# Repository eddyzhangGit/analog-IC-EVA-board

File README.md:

Imagine that you are an integrated circuit designer at university lab. You took 5 month to design a integrated chip and just get back from fabrication. you are excited to test it. You want to see whether it will power up and how much power it will consume at certain states.

In order to test it and you most likely will need the following to configure your chip.

 - A positive/negative bias voltage to bias the transistor. 
 - A precision bias current for your current mirror.
 - Digital host to load the chip register.
 - Adjustable Voltage supply to power the chip.
 - E load to set current consumptions.

Instead of spending a large amount of time designing all the biasing circuit your self 
or worse, you use a lab equipments such as Aglient power supply,  Total phase digital host, E-load which cost thousands of dollars.

Our Analog IC Equation Platform offers an solution for rapid IC Evaluation.

The board is equipped with 

- 4 x 50 mA and 2 x200 mA power supply 0.5V to 3V with current Sensing ability
- 4 x Positive Bias Voltage 0 -3 V with error less than 0.5mV
- 2 x Negative Bias Voltage -2.5 - 0 V with error less than 1mV
- 4 x Bias current 0 - 1000uA with error less than 0.5%
- 2 Programmable resistor, 2.5K and 10K, 256 taps each
- Digital that allows GPIO and SPI communication.

The board is designed with a accuracy much higher than traditional lab Requirement,  to meet the requirement of IC testing

A MAC OS app is developed to allow user to  configure the board with ease.

Lastly, python functions are available to allow user to write their own scripts for automated testing. 
(Detailed Examples are provided in the USER MANUEL)
 
if you found this board will be beneficial to your project, Feel free to contact me for more information.

Eddy Zhen Zhang

Eddy.zhang@mail.utoronto.ca
 | 647-676-8287

￼

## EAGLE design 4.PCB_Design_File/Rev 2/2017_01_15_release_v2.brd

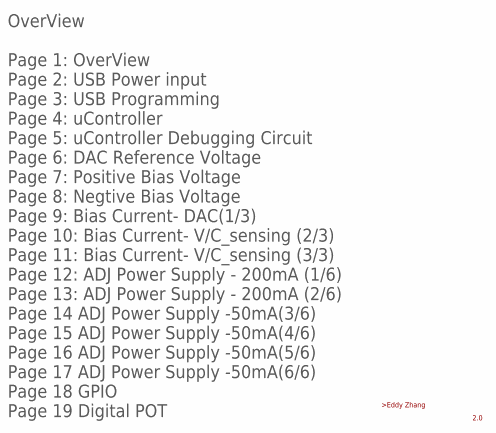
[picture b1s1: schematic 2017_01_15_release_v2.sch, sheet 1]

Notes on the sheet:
OverView Page 1: OverView Page 2: USB Power input Page 3: USB Programming Page 4: uController Page 5: uController Debugging Circuit Page 6: DAC Reference Voltage Page 7: Positive Bias Voltage Page 8: Negtive Bias Voltage Page 9: Bias Current- DAC(1/3) Page 10: Bias Current- V/C_sensing (2/3) Page 1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

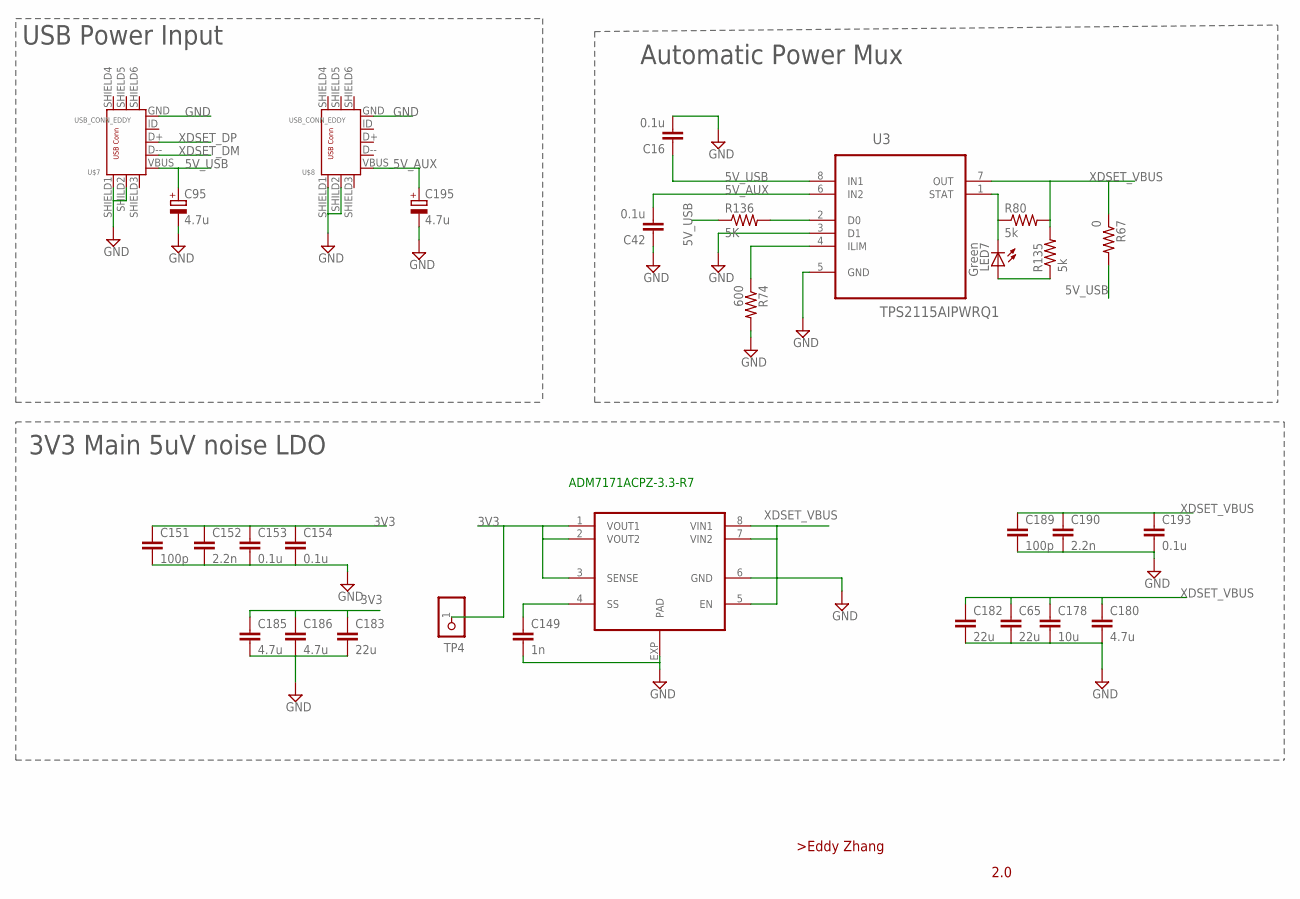
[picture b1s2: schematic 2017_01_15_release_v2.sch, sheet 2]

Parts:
C16, C42, C153, C154, C193: 0.1u; C0603
C65, C182, C183: 22u; C1210
C95, C195: 4.7u; A/3216-18R
C149: 1n; C0603
C151, C189: 100p; C0603
C152, C190: 2.2n; C0603
C178: 10u; C0805
C180, C185, C186: 4.7u; C0805
LED7: Green; LED-0603
R67: 0; R0603
R74: 600; R0603
R80, R135: 5k; R0603
R136: 5K; R0603
TP4: TEST_PIN2; 1X01
U3: TPS2115AIPWRQ1; SOP65P640X120-8N
U$7, U$8: USB_CONN_EDDY; USB_MICRO_EDDY
U$43: ADM7171; LFCSP8

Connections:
3V3: C151.1, C152.1, C153.1, C154.1, C183.1, C185.1, C186.1, TP4.1, U$43.1 (VOUT1), U$43.2 (VOUT2), U$43.3 (SENSE); also elsewhere on the board
5V_AUX: C42.2, C195.+, U3.6 (IN2), U$8.VBUS_ (VBUS); also elsewhere on the board
5V_USB: C16.1, C95.+, R67.2, R136.1, U3.8 (IN1), U$7.VBUS_ (VBUS); also elsewhere on the board
GND: C16.2, C42.1, C65.2, C95.-, C149.2, C151.2, C152.2, C153.2, C154.2, C178.2, C180.2, C182.2, C183.2, C185.2, C186.2, C189.2, C190.2, C193.2, C195.-, R74.2, U3.3 (D1), U3.5 (GND), U$7.GND, U$7.SHIELD1, U$7.SHILD2 (SHIELD2), U$8.GND, U$8.SHIELD1, U$8.SHILD2 (SHIELD2), U$43.6 (GND), U$43.EXP (PAD); also elsewhere on the board
unnamed: LED7.A, R135.1
unnamed: R136.2, U3.2 (D0)
unnamed: C149.1, U$43.4 (SS)
unnamed: LED7.C, R80.1, U3.1 (STAT)
unnamed: R74.1, U3.4 (ILIM)
XDSET_DM: U$7.D-- (D-); also elsewhere on the board
XDSET_DP: U$7.D+; also elsewhere on the board
XDSET_VBUS: C65.1, C178.1, C180.1, C182.1, C189.1, C190.1, C193.1, R67.1, R80.2, R135.2, U3.7 (OUT), U$43.5 (EN), U$43.7 (VIN2), U$43.8 (VIN1); also elsewhere on the board

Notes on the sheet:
USB Power Input
3V3 Main 5uV noise LDO
Automatic Power Mux
ADM7171ACPZ-3.3-R7

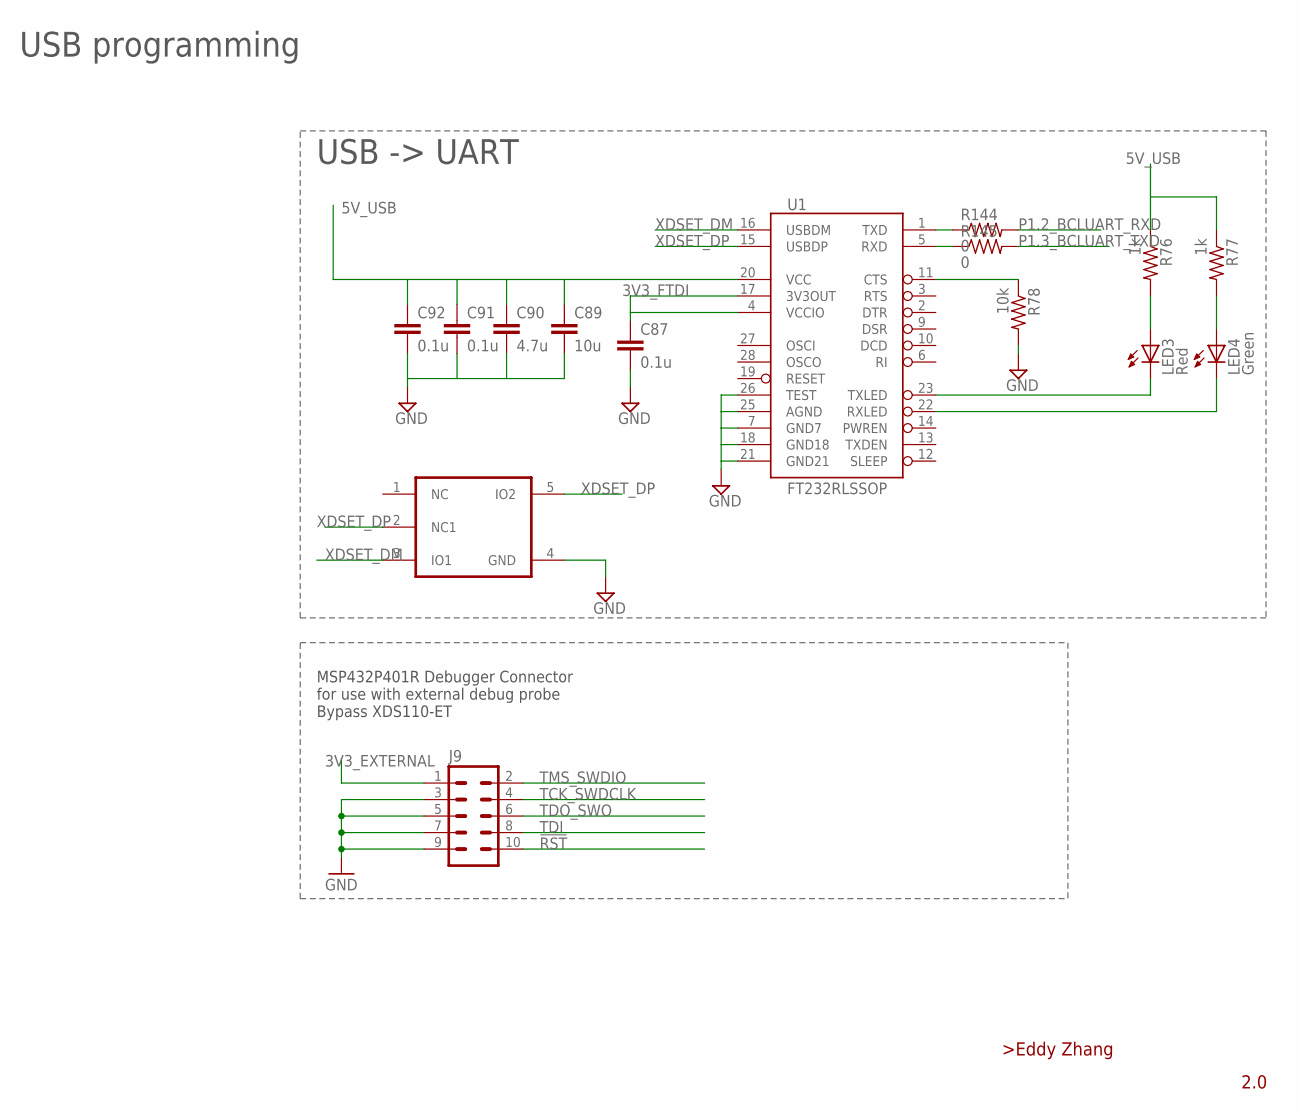
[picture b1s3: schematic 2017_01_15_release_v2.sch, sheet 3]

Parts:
C87, C91, C92: 0.1u; C0603
C89: 10u; C0805
C90: 4.7u; C0805
ESD_DIODE: TPD2E2U06; SOT_DRL_N5
J9: DEBUG_ARM-10; ARM-10
LED3: Red; LED-0603
LED4: Green; LED-0603
R76, R77: 1k; R0603
R78: 10k; R0603
R144, R145: 0; R0603
U1: FT232RLSSOP; SSOP28DB

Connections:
3V3_EXTERNAL: J9.1
3V3_FTDI: C87.1, U1.4 (VCCIO), U1.17 (3V3OUT)
5V_USB: C89.1, C90.1, C91.1, C92.1, R76.1, R77.1, U1.20 (VCC); also elsewhere on the board
!RST: J9.10; also elsewhere on the board
GND: C87.2, C89.2, C90.2, C91.2, C92.2, ESD_DIODE.4 (GND), J9.3, J9.5, J9.7, J9.9, R78.2, U1.7 (GND7), U1.18 (GND18), U1.21 (GND21), U1.25 (AGND), U1.26 (TEST); also elsewhere on the board
unnamed: R78.1, U1.11 (CTS)
unnamed: LED3.C, U1.23 (TXLED)
unnamed: LED4.C, U1.22 (RXLED)
unnamed: LED3.A, R76.2
unnamed: LED4.A, R77.2
P1.2_BCLUART_RXD: R144.2; also elsewhere on the board
P1.2_BCLUART_RXD_IC: R144.1, U1.1 (TXD)
P1.3_BCLUART_TXD: R145.2; also elsewhere on the board
P1.3_BCLUART_TXD_IC: R145.1, U1.5 (RXD)
TCK_SWDCLK: J9.4; also elsewhere on the board
TDI: J9.8; also elsewhere on the board
TDO_SWO: J9.6; also elsewhere on the board
TMS_SWDIO: J9.2; also elsewhere on the board
XDSET_DM: ESD_DIODE.3 (IO1), U1.16 (USBDM); also elsewhere on the board
XDSET_DP: ESD_DIODE.2 (NC1), ESD_DIODE.5 (IO2), U1.15 (USBDP); also elsewhere on the board

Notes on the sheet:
USB programming
USB -> UART
MSP432P401R Debugger Connector for use with external debug probe Bypass XDS110-ET

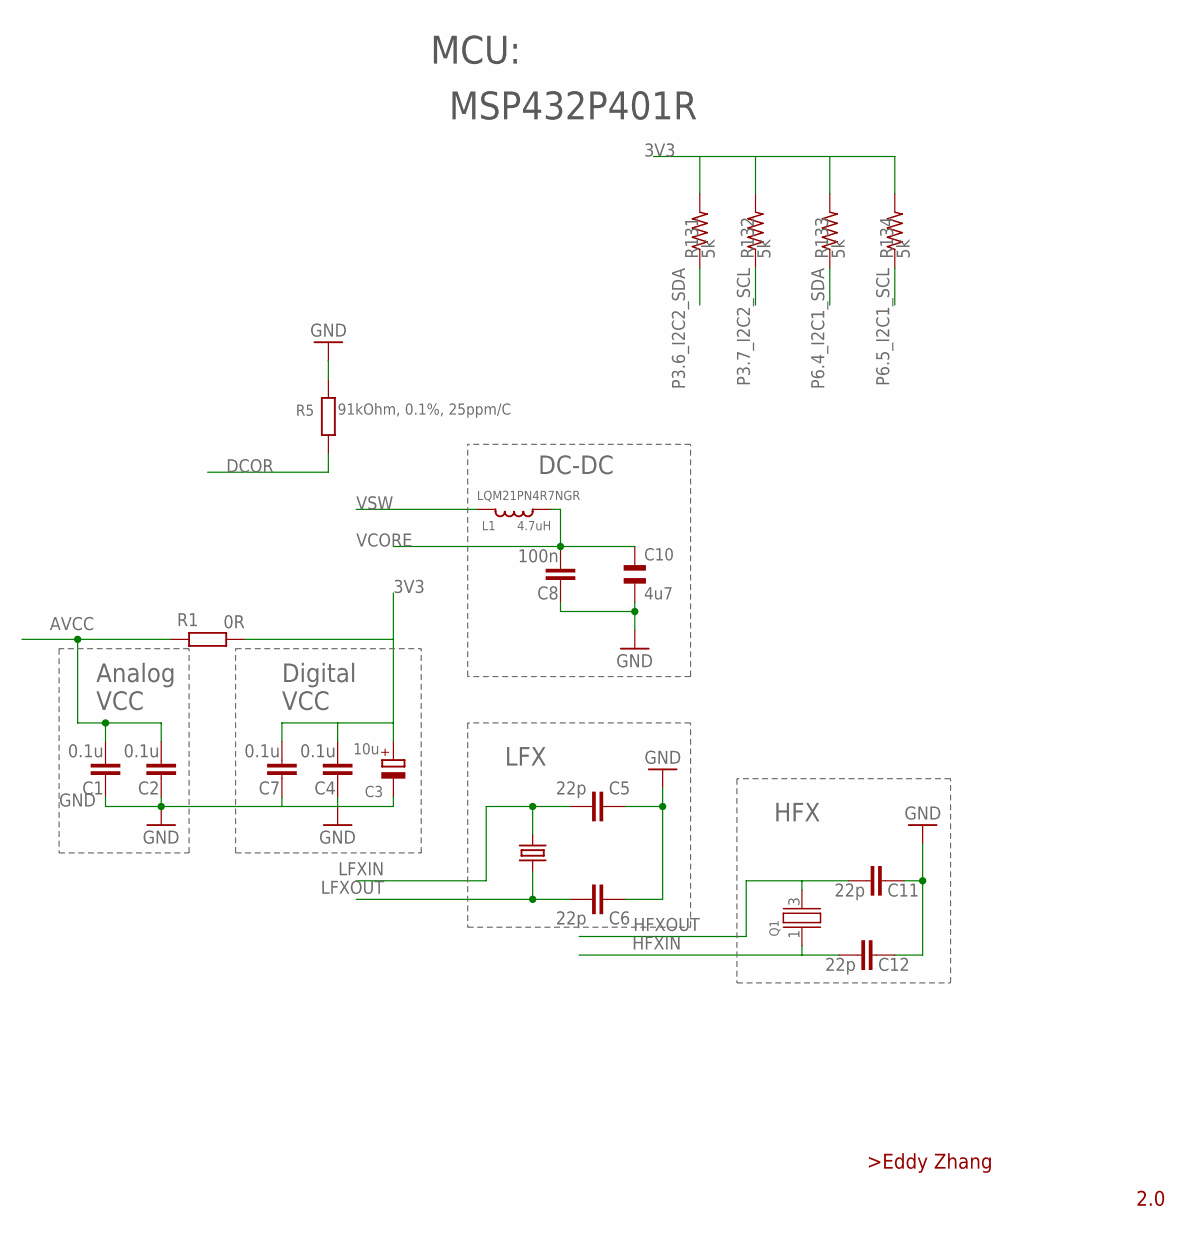
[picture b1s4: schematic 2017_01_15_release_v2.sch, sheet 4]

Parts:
32KHZ: FC-135; FC-135_32KHZ
C1, C2, C4, C7: 0.1u; C0603K
C3: 10u; A/3216-18R
C5, C6: 22p; C0603
C8: 100n; C0603K
C10: 4u7; CSMD0805
C11, C12: 22p; C0603K
L1: 4.7uH; 0806
Q1: CRYSTALEPSON_FA-238; FA-238
R1: 0R; R0603
R5: 91kOhm, 0.1%, 25ppm/C; 0805
R131, R132, R133, R134: 5k; R0603

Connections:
3V3: C3.+, C4.1, C7.1, R1.1, R131.2, R132.2, R133.2, R134.2; also elsewhere on the board
AVCC: C1.1, C2.1, R1.2; also elsewhere on the board
DCOR: R5.1; also elsewhere on the board
GND: C1.2, C2.2, C3.-, C4.2, C5.2, C6.2, C7.2, C8.2, C10.2, C11.2, C12.2, R5.2; also elsewhere on the board
HFXIN: C12.1, Q1.1; also elsewhere on the board
HFXOUT: C11.1, Q1.3 (2); also elsewhere on the board
LFXIN: 32KHZ.P$2 (2), C5.1; also elsewhere on the board
LFXOUT: 32KHZ.P$1 (1), C6.1; also elsewhere on the board
P3.6_I2C2_SDA: R131.1; also elsewhere on the board
P3.7_I2C2_SCL: R132.1; also elsewhere on the board
P6.4_I2C1_SDA: R133.1; also elsewhere on the board
P6.5_I2C1_SCL: R134.1; also elsewhere on the board
VCORE: C8.1, C10.1, L1.1; also elsewhere on the board
VSW: L1.2; also elsewhere on the board

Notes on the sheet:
MCU:
LQM21PN4R7NGR
HFX
LFX
Analog
VCC
Digital
DC-DC
MSP432P401R

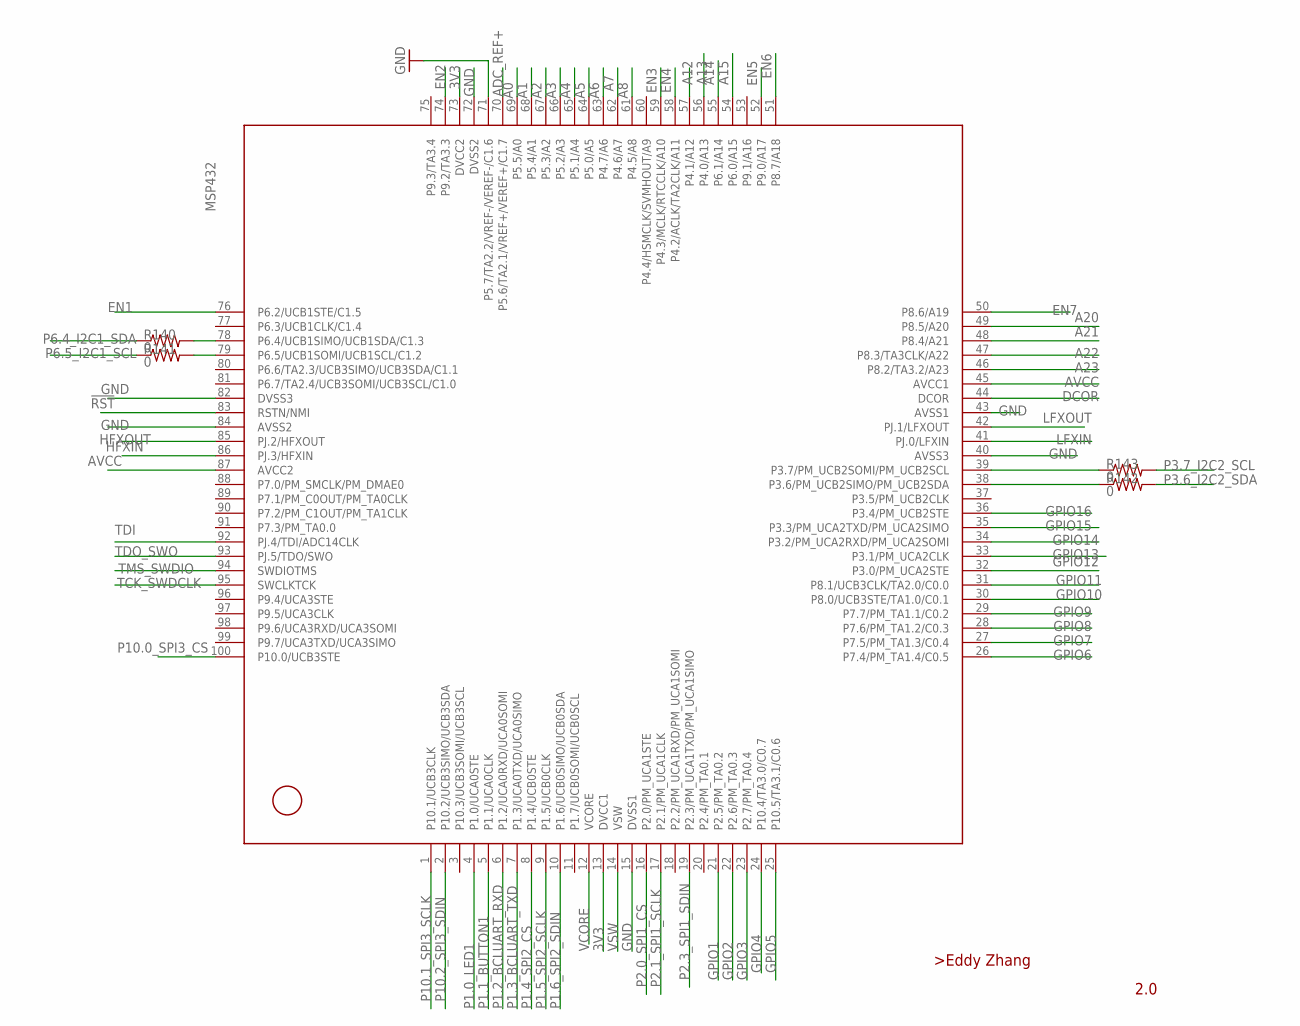
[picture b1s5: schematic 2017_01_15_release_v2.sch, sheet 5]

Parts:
MSP432: MSP432P401XPZ; LQFP100
R140, R141, R142, R143: 0; R0603

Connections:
3V3: MSP432.13 (DVCC1), MSP432.73 (DVCC2); also elsewhere on the board
!RST: MSP432.83 (RSTN/NMI); also elsewhere on the board
A0: MSP432.69 (P5.5/A0); also elsewhere on the board
A1: MSP432.68 (P5.4/A1); also elsewhere on the board
A2: MSP432.67 (P5.3/A2); also elsewhere on the board
A3: MSP432.66 (P5.2/A3); also elsewhere on the board
A4: MSP432.65 (P5.1/A4); also elsewhere on the board
A5: MSP432.64 (P5.0/A5); also elsewhere on the board
A6: MSP432.63 (P4.7/A6); also elsewhere on the board
A7: MSP432.62 (P4.6/A7); also elsewhere on the board
A8: MSP432.61 (P4.5/A8); also elsewhere on the board
A12: MSP432.57 (P4.1/A12); also elsewhere on the board
A13: MSP432.56 (P4.0/A13); also elsewhere on the board
A14: MSP432.55 (P6.1/A14); also elsewhere on the board
A15: MSP432.54 (P6.0/A15); also elsewhere on the board
A20: MSP432.49 (P8.5/A20); also elsewhere on the board
A21: MSP432.48 (P8.4/A21); also elsewhere on the board
A22: MSP432.47 (P8.3/TA3CLK/A22); also elsewhere on the board
A23: MSP432.46 (P8.2/TA3.2/A23); also elsewhere on the board
ADC_REF+: MSP432.70 (P5.6/TA2.1/VREF+/VEREF+/C1.7); also elsewhere on the board
AVCC: MSP432.45 (AVCC1), MSP432.87 (AVCC2); also elsewhere on the board
DCOR: MSP432.44 (DCOR); also elsewhere on the board
EN1: MSP432.76 (P6.2/UCB1STE/C1.5); also elsewhere on the board
EN2: MSP432.74 (P9.2/TA3.3); also elsewhere on the board
EN3: MSP432.59 (P4.3/MCLK/RTCCLK/A10); also elsewhere on the board
EN4: MSP432.58 (P4.2/ACLK/TA2CLK/A11); also elsewhere on the board
EN5: MSP432.52 (P9.0/A17); also elsewhere on the board
EN6: MSP432.51 (P8.7/A18); also elsewhere on the board
EN7: MSP432.50 (P8.6/A19); also elsewhere on the board
GND: MSP432.15 (DVSS1), MSP432.40 (AVSS3), MSP432.43 (AVSS1), MSP432.71 (P5.7/TA2.2/VREF-/VEREF-/C1.6), MSP432.72 (DVSS2), MSP432.82 (DVSS3), MSP432.84 (AVSS2); also elsewhere on the board
GPIO1: MSP432.21 (P2.5/PM_TA0.2); also elsewhere on the board
GPIO2: MSP432.22 (P2.6/PM_TA0.3); also elsewhere on the board
GPIO3: MSP432.23 (P2.7/PM_TA0.4); also elsewhere on the board
GPIO4: MSP432.24 (P10.4/TA3.0/C0.7); also elsewhere on the board
GPIO5: MSP432.25 (P10.5/TA3.1/C0.6); also elsewhere on the board
GPIO6: MSP432.26 (P7.4/PM_TA1.4/C0.5); also elsewhere on the board
GPIO7: MSP432.27 (P7.5/PM_TA1.3/C0.4); also elsewhere on the board
GPIO8: MSP432.28 (P7.6/PM_TA1.2/C0.3); also elsewhere on the board
GPIO9: MSP432.29 (P7.7/PM_TA1.1/C0.2); also elsewhere on the board
GPIO10: MSP432.30 (P8.0/UCB3STE/TA1.0/C0.1); also elsewhere on the board
GPIO11: MSP432.31 (P8.1/UCB3CLK/TA2.0/C0.0); also elsewhere on the board
GPIO12: MSP432.32 (P3.0/PM_UCA2STE); also elsewhere on the board
GPIO13: MSP432.33 (P3.1/PM_UCA2CLK); also elsewhere on the board
GPIO14: MSP432.34 (P3.2/PM_UCA2RXD/PM_UCA2SOMI); also elsewhere on the board
GPIO15: MSP432.35 (P3.3/PM_UCA2TXD/PM_UCA2SIMO); also elsewhere on the board
GPIO16: MSP432.36 (P3.4/PM_UCB2STE); also elsewhere on the board
HFXIN: MSP432.86 (PJ.3/HFXIN); also elsewhere on the board
HFXOUT: MSP432.85 (PJ.2/HFXOUT); also elsewhere on the board
LFXIN: MSP432.41 (PJ.0/LFXIN); also elsewhere on the board
LFXOUT: MSP432.42 (PJ.1/LFXOUT); also elsewhere on the board
P1.0_LED1: MSP432.4 (P1.0/UCA0STE); also elsewhere on the board
P1.1_BUTTON1: MSP432.5 (P1.1/UCA0CLK); also elsewhere on the board
P1.2_BCLUART_RXD: MSP432.6 (P1.2/UCA0RXD/UCA0SOMI); also elsewhere on the board
P1.3_BCLUART_TXD: MSP432.7 (P1.3/UCA0TXD/UCA0SIMO); also elsewhere on the board
P1.4_SPI2_CS: MSP432.8 (P1.4/UCB0STE); also elsewhere on the board
P1.5_SPI2_SCLK: MSP432.9 (P1.5/UCB0CLK); also elsewhere on the board
P1.6_SPI2_SDIN: MSP432.10 (P1.6/UCB0SIMO/UCB0SDA); also elsewhere on the board
P2.0_SPI1_CS: MSP432.16 (P2.0/PM_UCA1STE); also elsewhere on the board
P2.1_SPI1_SCLK: MSP432.17 (P2.1/PM_UCA1CLK); also elsewhere on the board
P2.3_SPI1_SDIN: MSP432.19 (P2.3/PM_UCA1TXD/PM_UCA1SIMO); also elsewhere on the board
P3.6_I2C2_SDA: R142.2; also elsewhere on the board
P3.6_I2C2_SDA_IC: MSP432.38 (P3.6/PM_UCB2SIMO/PM_UCB2SDA), R142.1
P3.7_I2C2_SCL: R143.2; also elsewhere on the board
P3.7_I2C2_SCL_IC: MSP432.39 (P3.7/PM_UCB2SOMI/PM_UCB2SCL), R143.1
P6.4_I2C1_SDA: R140.1; also elsewhere on the board
P6.4_I2C1_SDA_IC: MSP432.78 (P6.4/UCB1SIMO/UCB1SDA/C1.3), R140.2
P6.5_I2C1_SCL: R141.1; also elsewhere on the board
P6.5_I2C1_SCL_IC: MSP432.79 (P6.5/UCB1SOMI/UCB1SCL/C1.2), R141.2
P10.0_SPI3_CS: MSP432.100 (P10.0/UCB3STE); also elsewhere on the board
P10.1_SPI3_SCLK: MSP432.1 (P10.1/UCB3CLK); also elsewhere on the board
P10.2_SPI3_SDIN: MSP432.2 (P10.2/UCB3SIMO/UCB3SDA); also elsewhere on the board
TCK_SWDCLK: MSP432.95 (SWCLKTCK); also elsewhere on the board
TDI: MSP432.92 (PJ.4/TDI/ADC14CLK); also elsewhere on the board
TDO_SWO: MSP432.93 (PJ.5/TDO/SWO); also elsewhere on the board
TMS_SWDIO: MSP432.94 (SWDIOTMS); also elsewhere on the board
VCORE: MSP432.12 (VCORE); also elsewhere on the board
VSW: MSP432.14 (VSW); also elsewhere on the board

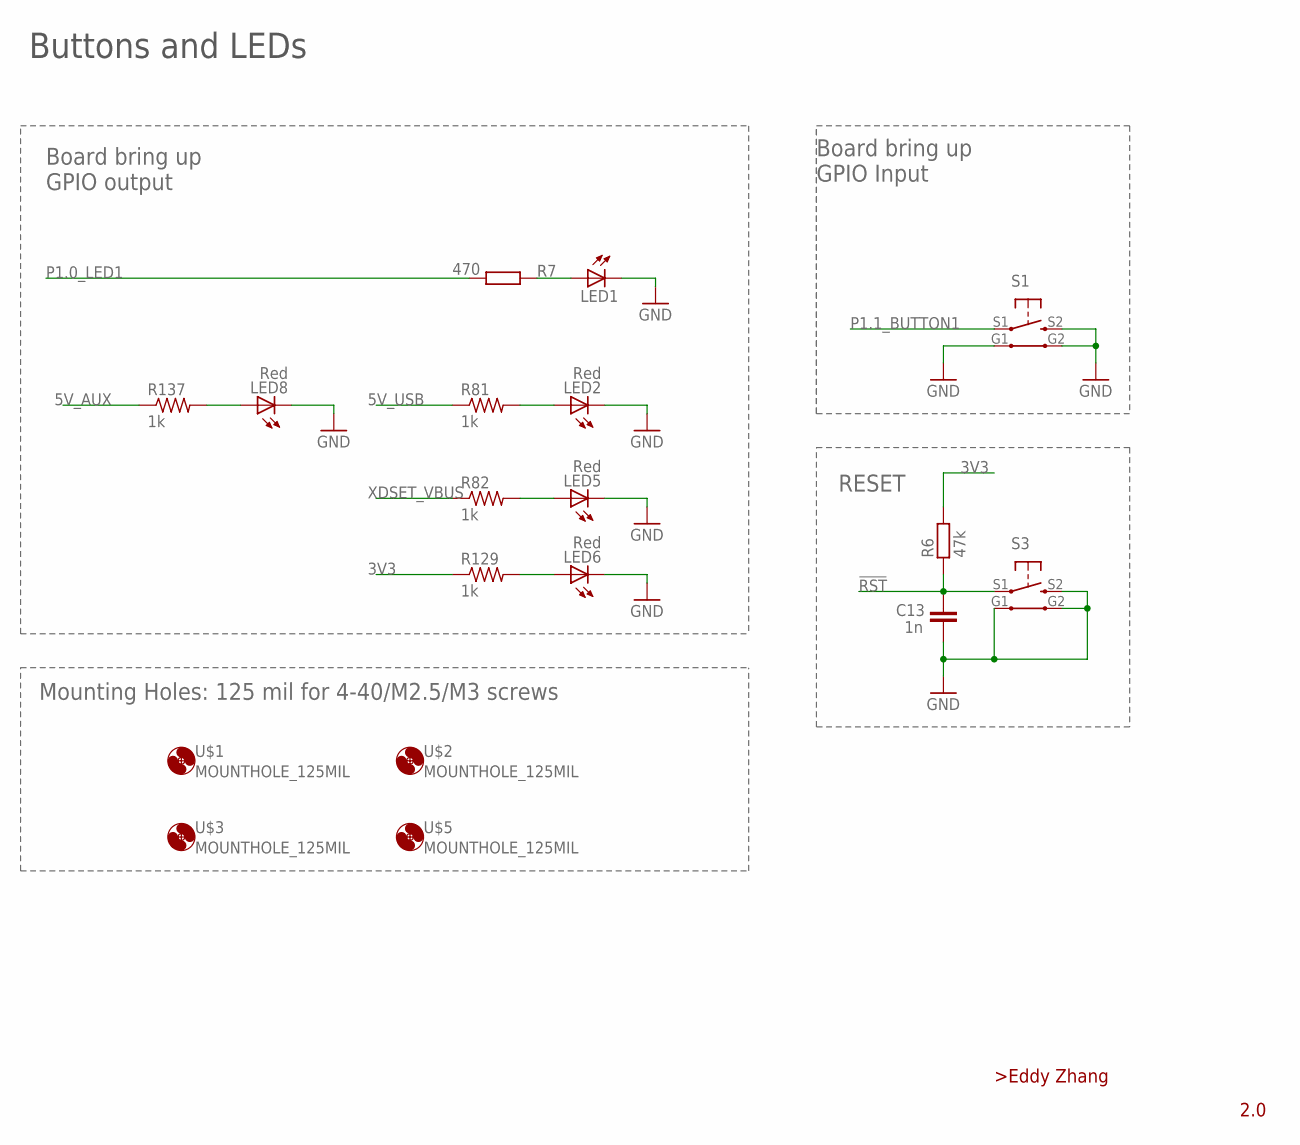
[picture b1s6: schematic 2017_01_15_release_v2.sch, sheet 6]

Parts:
C13: 1n; C0603
LED1: LEDCHIPLED_0603; CHIPLED_0603
LED2, LED5, LED6, LED8: Red; LED-0603
R6: 47k; R0603
R7: 470; R0603
R81, R82, R129, R137: 1k; R0603
S1, S3: TS-1188E
U$1, U$2, U$3, U$5: MOUNTHOLE_125MIL

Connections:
3V3: R6.2, R129.1; also elsewhere on the board
5V_AUX: R137.1; also elsewhere on the board
5V_USB: R81.1; also elsewhere on the board
!RST: C13.1, R6.1, S3.S1; also elsewhere on the board
GND: C13.2, LED1.C, LED2.C, LED5.C, LED6.C, LED8.C, S1.G1, S1.G2, S1.S2 (S), S3.G1, S3.G2, S3.S2 (S); also elsewhere on the board
unnamed: LED1.A, R7.2
unnamed: LED8.A, R137.2
unnamed: LED6.A, R129.2
unnamed: LED2.A, R81.2
unnamed: LED5.A, R82.2
P1.0_LED1: R7.1; also elsewhere on the board
P1.1_BUTTON1: S1.S1; also elsewhere on the board
XDSET_VBUS: R82.1; also elsewhere on the board

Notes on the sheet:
Board bring up GPIO Input
RESET
Buttons and LEDs
Mounting Holes: 125 mil for 4-40/M2.5/M3 screws
Board bring up GPIO output

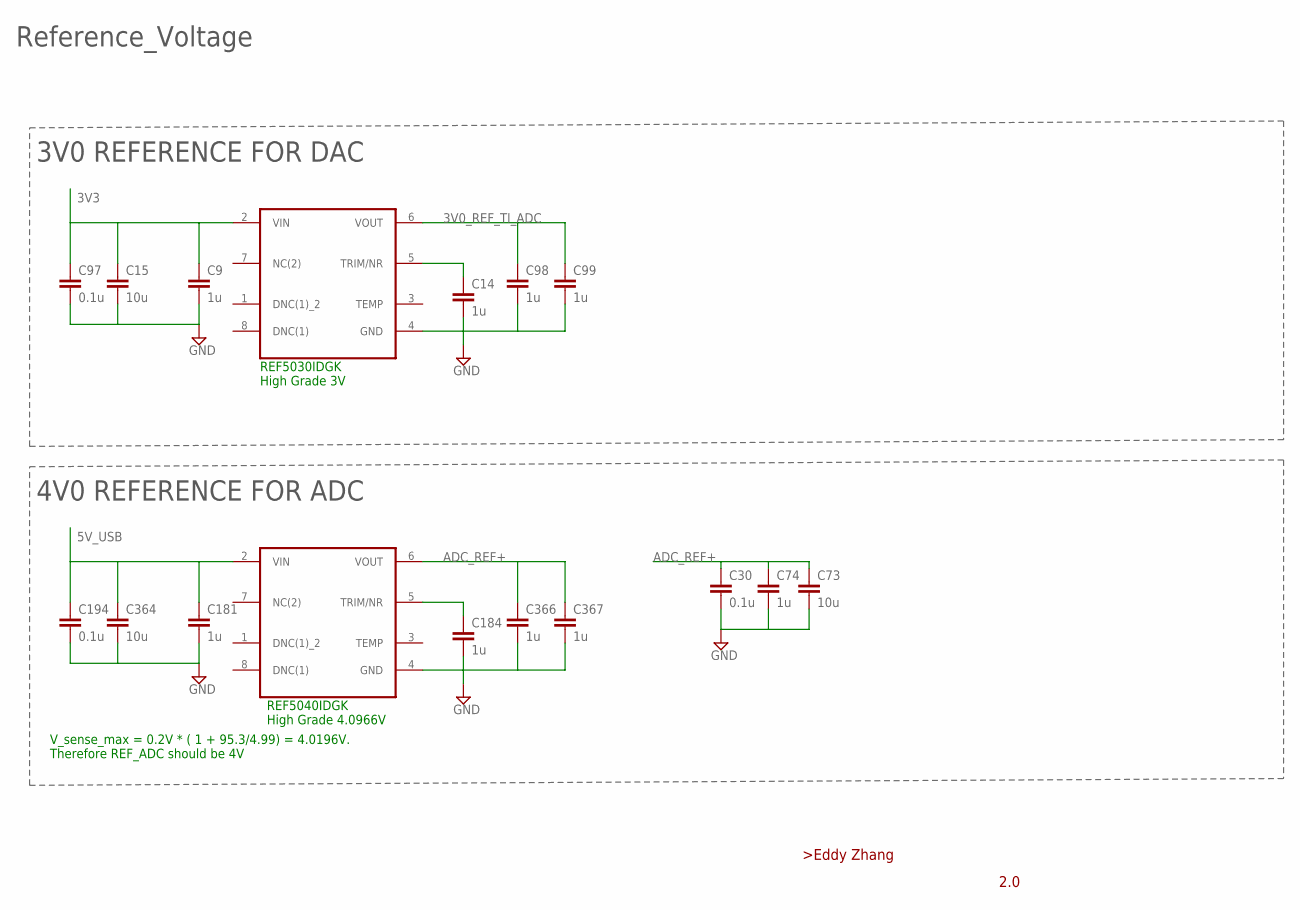
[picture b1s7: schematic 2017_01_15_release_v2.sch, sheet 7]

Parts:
C9, C98, C99, C181, C184, C366, C367: 1u; C0603
C14, C74: 1u; C0603K
C15, C364: 10u; C0805
C30: 0.1u; C0603K
C73: 10u; C0805K
C97, C194: 0.1u; C0603
REF5030, REF5040: REF5025AID; SOIC127P600X175-8N

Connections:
3V0_REF_TI_ADC: C98.1, C99.1, REF5030.6 (VOUT); also elsewhere on the board
3V3: C9.1, C15.1, C97.1, REF5030.2 (VIN); also elsewhere on the board
5V_USB: C181.1, C194.1, C364.1, REF5040.2 (VIN); also elsewhere on the board
ADC_REF+: C30.1, C73.1, C74.1, C366.1, C367.1, REF5040.6 (VOUT); also elsewhere on the board
GND: C9.2, C14.2, C15.2, C30.2, C73.2, C74.2, C97.2, C98.2, C99.2, C181.2, C184.2, C194.2, C364.2, C366.2, C367.2, REF5030.4 (GND), REF5040.4 (GND); also elsewhere on the board
unnamed: C14.1, REF5030.5 (TRIM/NR)
unnamed: C184.1, REF5040.5 (TRIM/NR)

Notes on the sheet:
Reference_Voltage
3V0 REFERENCE FOR DAC
4V0 REFERENCE FOR ADC
V_sense_max = 0.2V * ( 1 + 95.3/4.99) = 4.0196V. Therefore REF_ADC should be 4V
REF5040IDGK High Grade 4.0966V
REF5030IDGK High Grade 3V

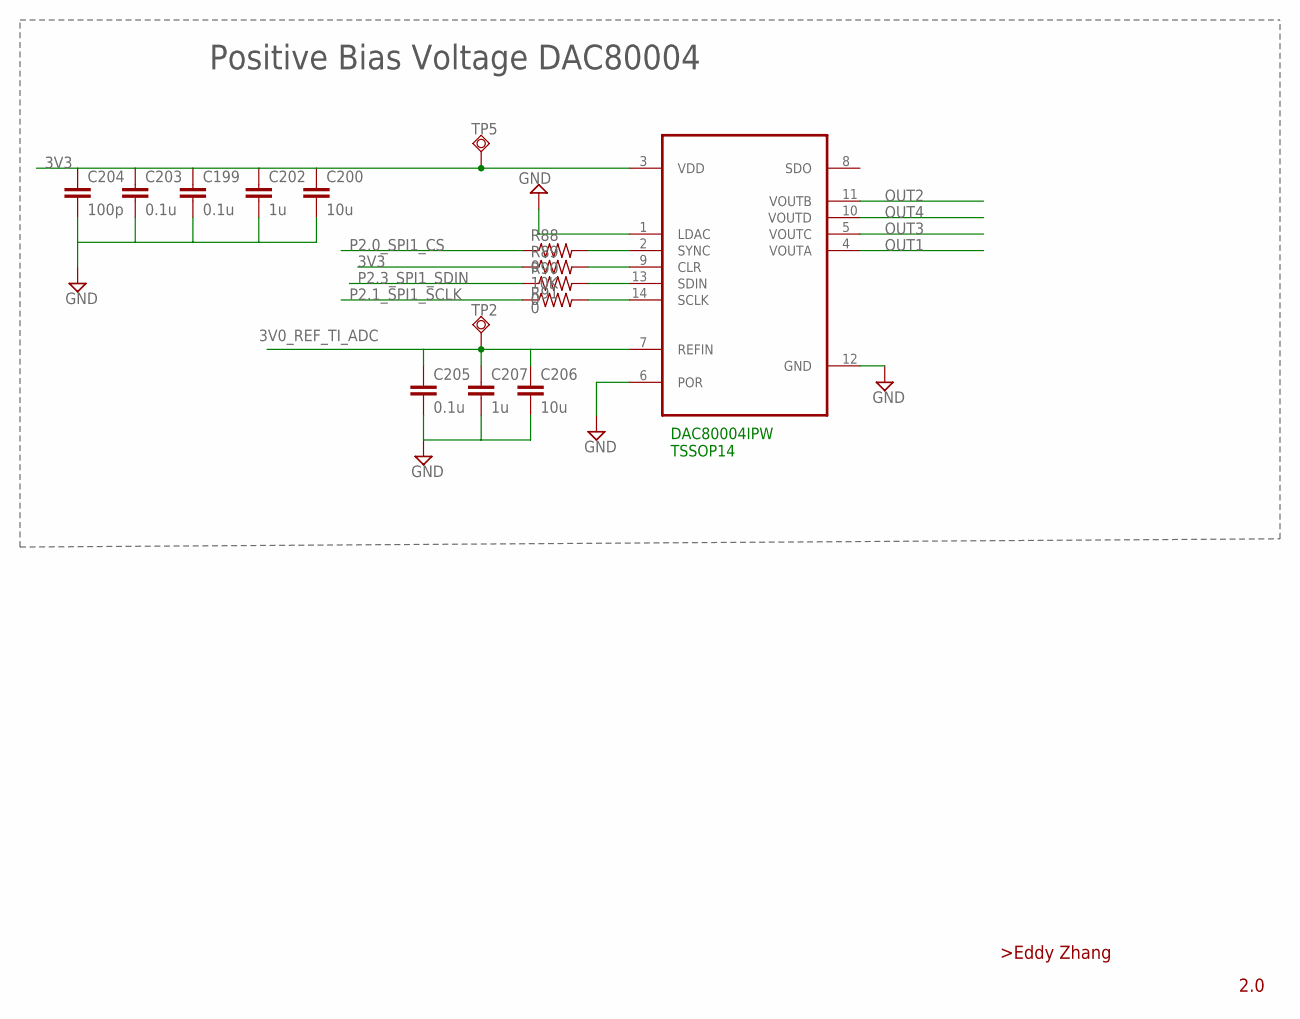
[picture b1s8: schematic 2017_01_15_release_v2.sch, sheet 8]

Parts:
C199, C203: 0.1u; C0603K
C200, C206: 10u; C0805
C202, C207: 1u; C0603
C204: 100p; C0603K
C205: 0.1u; C0603
R88, R90, R91: 0; R0603
R89: 10K; R0603
TP2, TP5: TPSQTP20R; TP20R
U$11: DAC80004; TSSOP14

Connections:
3V0_REF_TI_ADC: C205.1, C206.1, C207.1, TP2.TP, U$11.7 (REFIN); also elsewhere on the board
3V3: C199.1, C200.1, C202.1, C203.1, C204.1, R89.1, TP5.TP, U$11.3 (VDD); also elsewhere on the board
GND: C199.2, C200.2, C202.2, C203.2, C204.2, C205.2, C206.2, C207.2, U$11.1 (LDAC), U$11.6 (POR), U$11.12 (GND); also elsewhere on the board
unnamed: R90.2, U$11.13 (SDIN)
unnamed: R91.2, U$11.14 (SCLK)
unnamed: R89.2, U$11.9 (CLR)
unnamed: R88.2, U$11.2 (SYNC)
OUT1: U$11.4 (VOUTA); also elsewhere on the board
OUT2: U$11.11 (VOUTB); also elsewhere on the board
OUT3: U$11.5 (VOUTC); also elsewhere on the board
OUT4: U$11.10 (VOUTD); also elsewhere on the board
P2.0_SPI1_CS: R88.1; also elsewhere on the board
P2.1_SPI1_SCLK: R91.1; also elsewhere on the board
P2.3_SPI1_SDIN: R90.1; also elsewhere on the board

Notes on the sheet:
Positive Bias Voltage DAC80004
DAC80004IPW TSSOP14

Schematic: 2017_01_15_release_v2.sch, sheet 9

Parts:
C49, C50, C188, C210, C237, C372: 0.1u; C0603
C138, C208, C216: 0.1u; C0603K
C139, C211, C220, C240, C370, C373: 10u; C0805
C177, C212, C215, C242, C371: 1u; C0603
C198: 1u; C0603K
C209: 100p; C0603K
C221, C241: 22u; C1206K
C222, C235, C243, C244: 4.7u; C0805
C238: 10n; C0603
R75, R85, R86, R93: 0; R0603
R79: 10K; R0603
TP6, TP7: TPSQTP20R; TP20R
U$12: DAC80004; TSSOP14
U$41, U$45: LT5400; MSOP8
U$42: TSZ122; SO08
U$56: MAX1697; SOT23-6
U$57: TPS723-Q1; SOT23-5

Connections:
3V0_REF_TI_ADC: C210.1, C211.1, C212.1, TP7.TP, U$12.7 (REFIN); also elsewhere on the board
3V3: C138.1, C139.1, C198.1, C208.1, C209.1, C215.1, C216.1, C220.1, C221.1, C371.1, C372.1, C373.1, R79.1, TP6.TP, U$12.3 (VDD), U$42.8 (VCC+), U$56.2 (VIN), U$56.5 (SHDN); also elsewhere on the board
-2V5: C177.1, C188.1, C243.1, C244.1, C370.1, U$42.4 (VCC-), U$57.5 (OUT)
-3V3_NOISY: C237.1, C240.1, C241.1, C242.1, U$56.1 (OUT), U$57.2 (IN), U$57.3 (EN)
-OUT2: C49.2, U$41.1 (R1+), U$41.2 (R2+), U$42.1 (OUT1); also elsewhere on the board
-OUT4: C50.2, U$42.7 (OUT2), U$45.7 (R2-), U$45.8 (R1-); also elsewhere on the board
GND: C138.2, C139.2, C177.2, C188.2, C198.2, C208.2, C209.2, C210.2, C211.2, C212.2, C215.2, C216.2, C220.2, C221.2, C237.2, C238.2, C240.2, C241.2, C242.2, C243.2, C244.2, C370.2, C371.2, C372.2, C373.2, R93.1, U$12.1 (LDAC), U$12.12 (GND), U$42.3 (IN1+), U$42.5 (IN2+), U$56.4 (GND), U$57.1 (GND); also elsewhere on the board
unnamed: R93.2, U$12.6 (POR)
unnamed: C238.1, U$57.4 (NR)
unnamed: R75.2, U$12.2 (SYNC)
unnamed: R79.2, U$12.9 (CLR)
unnamed: R85.2, U$12.13 (SDIN)
unnamed: R86.2, U$12.14 (SCLK)
unnamed: C49.1, U$41.5 (R4-), U$41.6 (R3-), U$41.7 (R2-), U$41.8 (R1-), U$42.2 (IN1-)
unnamed: C222.1, C235.1, U$56.6 (C+)
unnamed: C222.2, C235.2, U$56.3 (C-)
unnamed: C50.1, U$42.6 (IN2-), U$45.1 (R1+), U$45.2 (R2+), U$45.3 (R3+), U$45.4 (R4+)
P10.0_SPI3_CS: R75.1; also elsewhere on the board
P10.1_SPI3_SCLK: R86.1; also elsewhere on the board
P10.2_SPI3_SDIN: R85.1; also elsewhere on the board
VOUTA: U$12.4 (VOUTA), U$41.3 (R3+), U$41.4 (R4+)
VOUTC: U$12.5 (VOUTC), U$45.5 (R4-), U$45.6 (R3-)

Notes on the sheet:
Negtive Bias Voltage DAC80004
Charge pump+LDO -2.5V
Inverting Opamp(1+2)
DAC80004IPW TSSOP14
LT5400ACMS8E-1
TPS72325QDBVRQ1 (Fixed 2.5V version)
TSZ122IDT (SO8)

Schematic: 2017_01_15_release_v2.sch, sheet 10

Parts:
C18, C219: 0.1u; C0603K
C217: 10u; C0805K
C239: 100p; C0603
C245: 0.1u; C0603
C246: 10u; C0805
C247: 1u; C0603
R94, R96, R97: 0; R0603
R95: 10K; R0603
TP1, TP8: TPSQTP20R; TP20R
U$14: DAC80004; TSSOP14

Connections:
3V0_REF_TI_ADC: C245.1, C246.1, C247.1, TP1.TP, U$14.7 (REFIN); also elsewhere on the board
3V3: C18.1, C217.1, C219.1, C239.1, R95.1, TP8.TP, U$14.3 (VDD); also elsewhere on the board
GND: C18.2, C217.2, C219.2, C239.2, C245.2, C246.2, C247.2, U$14.1 (LDAC), U$14.6 (POR), U$14.12 (GND); also elsewhere on the board
unnamed: R97.2, U$14.14 (SCLK)
unnamed: R94.2, U$14.2 (SYNC)
unnamed: R95.2, U$14.9 (CLR)
unnamed: R96.2, U$14.13 (SDIN)
P1.4_SPI2_CS: R94.1; also elsewhere on the board
P1.5_SPI2_SCLK: R97.1; also elsewhere on the board
P1.6_SPI2_SDIN: R96.1; also elsewhere on the board
V/C_1: U$14.4 (VOUTA); also elsewhere on the board
V/C_2: U$14.11 (VOUTB); also elsewhere on the board
V/C_3: U$14.5 (VOUTC); also elsewhere on the board
V/C_4: U$14.10 (VOUTD); also elsewhere on the board

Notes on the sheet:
Bias Current (1/3) DAC
DAC80004IPW TSSOP14

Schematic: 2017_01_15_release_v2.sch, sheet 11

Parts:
C23, C24, C253, C259: 10n; C0603
C25, C248: 100p; C0603
C26, C249, C252, C256, C260, C263: 0.1u; C0603
C136, C137: 2.2n; C0603
C250, C254, C257, C261: 10u; C0805
C251, C255, C258, C262: 1u; C0603
Q3, Q4: SI2304DDS; SOT23-BEC
R8, R18, R19, R21: 200; R0805
R9: 1.5k; R0603
R20: 1.5k; R0805
R22, R26, R99, R130: 4.99K; R0603
R23, R100: 45.3K; R0603
R24, R121: 0; R0603
R25, R122: 95.3K; R0603
R27, R83: 100; R0603
SV8, SV9: MA03-1
TP10, TP11, TP13, TP14, TP43, TP44, TP45, TP46: TPSQTP20R; TP20R
U$15, U$16, U$58, U$59: OPA333DVT; SC70

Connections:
3V3: C26.1, C249.1, C250.1, C251.1, C254.2, C255.2, C256.2, C257.1, C258.1, C261.2, C262.2, C263.2, SV8.1, SV9.1, U$15.5 (V+), U$16.5 (V+), U$58.5 (V+), U$59.5 (V+); also elsewhere on the board
A21: C137.1, R27.1, TP11.TP; also elsewhere on the board
A22: C136.1, R83.1, TP14.TP; also elsewhere on the board
GND: C25.2, C26.2, C136.2, C137.2, C248.2, C249.2, C250.2, C251.2, C253.2, C254.1, C255.1, C256.1, C257.2, C258.2, C259.2, C261.1, C262.1, C263.1, R18.1, R21.1, R22.2, R26.2, R99.2, R130.2, U$15.2 (V-), U$16.2 (V-), U$58.2 (V-), U$59.2 (V-); also elsewhere on the board
IOUT1: SV9.3; also elsewhere on the board
IOUT2: SV8.3; also elsewhere on the board
unnamed: Q3.B, R19.2
unnamed: C248.1, R99.1, R100.2, TP44.TP, U$15.1 (+IN)
unnamed: Q4.B, R8.2
unnamed: Q4.C, SV9.2
unnamed: C23.2, R9.1, U$15.3 (-IN)
unnamed: Q3.C, SV8.2
unnamed: C25.1, R22.1, R23.2, TP46.TP, U$58.1 (+IN)
unnamed: C24.1, R19.1, U$58.4 (OUT)
unnamed: C259.1, Q3.E, R20.2, R21.2, R24.2
unnamed: C24.2, R20.1, U$58.3 (-IN)
unnamed: R24.1, TP13.TP, U$59.1 (+IN)
unnamed: C260.2, R25.2, R26.1, U$59.3 (-IN)
unnamed: C260.1, R25.1, R83.2, U$59.4 (OUT)
unnamed: C23.1, R8.1, U$15.4 (OUT)
unnamed: C253.1, Q4.E, R9.2, R18.2, R121.2
unnamed: R121.1, TP10.TP, U$16.1 (+IN)
unnamed: C252.2, R122.2, R130.1, U$16.3 (-IN)
unnamed: C252.1, R27.2, R122.1, U$16.4 (OUT)
V/C_1: R100.1, TP43.TP; also elsewhere on the board
V/C_2: R23.1, TP45.TP; also elsewhere on the board

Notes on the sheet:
Low side Current Sensing
Voltage to Current Circuit
Bias Current (3/3)
V = V_in * (4.99/(45.3+4.99)) V = Vin * 0.99224 DAC output 0-2V ---> 0 to 0.2V at R31
0- 0.2V @R31 ---0uA - 1000uA
V_sense_max = 0.2V * ( 1 + 95.3/4.99) = 4.0196V. Therefore REF_ADC should be 4V
OPA33AIDCKR PACKGE : SC70(DCK)

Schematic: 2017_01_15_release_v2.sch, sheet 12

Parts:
C17, C28, C33, C38: 10n; C0603
C20, C34: 100p; C0603
C21: 0.1u; C0603K
C22, C36, C40, C192: 10u; C0805
C27, C31, C37, C41: 1u; C0603
C29, C32, C35, C39, C44: 0.1u; C0603
C176, C179: 2.2n; C0603
Q5, Q6: SI2304DDS; SOT23-BEC
R10, R12, R29, R31: 200; R0805
R11, R30: 1.5k; R0603
R13, R17, R32, R36: 4.99K; R0603
R14, R33: 45.3K; R0603
R15, R34: 0; R0603
R16, R35: 95.3K; R0603
R28, R37: 100; R0603
SV6, SV7: MA03-1
TP3, TP9, TP16, TP19, TP47, TP48, TP49, TP50: TPSQTP20R; TP20R
U$17, U$18, U$19, U$20: OPA333DVT; SC70

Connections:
3V3: C21.1, C22.1, C27.1, C31.2, C32.2, C35.1, C36.1, C37.1, C40.2, C41.2, C44.2, C192.2, SV6.1, SV7.1, U$17.5 (V+), U$18.5 (V+), U$19.5 (V+), U$20.5 (V+); also elsewhere on the board
A20: C176.1, R28.1, TP3.TP; also elsewhere on the board
A23: C179.1, R37.1, TP9.TP; also elsewhere on the board
GND: C20.2, C21.2, C22.2, C27.2, C28.2, C31.1, C32.1, C34.2, C35.2, C36.2, C37.2, C38.2, C40.1, C41.1, C44.1, C176.2, C179.2, C192.1, R12.1, R13.2, R17.2, R31.1, R32.2, R36.2, U$17.2 (V-), U$18.2 (V-), U$19.2 (V-), U$20.2 (V-); also elsewhere on the board
IOUT3: SV7.3; also elsewhere on the board
IOUT4: SV6.3; also elsewhere on the board
unnamed: Q5.B, R10.2
unnamed: Q5.C, SV7.2
unnamed: C20.1, R13.1, R14.2, TP48.TP, U$17.1 (+IN)
unnamed: C17.1, R10.1, U$17.4 (OUT)
unnamed: C28.1, Q5.E, R11.2, R12.2, R15.2
unnamed: C17.2, R11.1, U$17.3 (-IN)
unnamed: R15.1, TP16.TP, U$18.1 (+IN)
unnamed: C39.2, R35.2, R36.1, U$20.3 (-IN)
unnamed: C29.2, R16.2, R17.1, U$18.3 (-IN)
unnamed: C29.1, R16.1, R28.2, U$18.4 (OUT)
unnamed: Q6.B, R29.2
unnamed: C34.1, R32.1, R33.2, TP50.TP, U$19.1 (+IN)
unnamed: C33.1, R29.1, U$19.4 (OUT)
unnamed: C38.1, Q6.E, R30.2, R31.2, R34.2
unnamed: C33.2, R30.1, U$19.3 (-IN)
unnamed: R34.1, TP19.TP, U$20.1 (+IN)
unnamed: Q6.C, SV6.2
unnamed: C39.1, R35.1, R37.2, U$20.4 (OUT)
V/C_3: R14.1, TP47.TP; also elsewhere on the board
V/C_4: R33.1, TP49.TP; also elsewhere on the board

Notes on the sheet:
Bias Current (3/3)
Low side Current Sensing
V/C _Circuit
V = V_in * (4.99/(45.3+4.99)) V = Vin * 0.99224 DAC output 0-2V ---> 0 to 0.2V at R31
V_sense_max = 0.2V * ( 1 + 95.3/4.99) = 4.0196V. Therefore REF_ADC should be 4V
0- 0.2V @R31 ---0uA - 1000uA
OPA33AIDCKR PACKGE : SC70(DCK)

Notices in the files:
4.PCB_Design_File/Rev 2/2017_01_15_release_v2.brd:
(C)2003 A. DANNENBERG
parts and their libraries:
SparkFun-Connectors_new: Licensing: Creative Commons ShareAlike 4.0 International - https://creativecommons.org/licenses/by-sa/4.0
